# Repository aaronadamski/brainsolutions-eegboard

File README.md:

# brainsolutions-eegboard
EEG Prototype Board for UCI Senior Design

For use in KiCAD EDA Suite.

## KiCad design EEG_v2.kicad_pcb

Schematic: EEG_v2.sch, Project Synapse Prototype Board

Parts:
JP1: JUMPER; 2x1 0.1\"
P1, P6: CONN_2; 2x1 0.1\"
P2, P4: CONN_8; 8x1 0.1\"
P3: USB_A
P5: CONN_5X2; 5x2 0.1\"
P7: CONN_1
R1: 10K; 0603
SW1: SWITCH_INV; SSSS810701
SW2: RESET

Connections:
+3.3V: R1.1; also elsewhere on the board
/Analog Frontend/AIN1N: P2.2; also elsewhere on the board
/Analog Frontend/AIN1P: P2.1; also elsewhere on the board
/Analog Frontend/AIN2N: P2.4; also elsewhere on the board
/Analog Frontend/AIN2P: P2.3; also elsewhere on the board
/Analog Frontend/AIN3N: P2.6; also elsewhere on the board
/Analog Frontend/AIN3P: P2.5; also elsewhere on the board
/Analog Frontend/AIN4N: P2.8; also elsewhere on the board
/Analog Frontend/AIN4P: P2.7; also elsewhere on the board
/Analog Frontend/AIN5N: P4.2; also elsewhere on the board
/Analog Frontend/AIN5P: P4.1; also elsewhere on the board
/Analog Frontend/AIN6N: P4.4; also elsewhere on the board
/Analog Frontend/AIN6P: P4.3; also elsewhere on the board
/Analog Frontend/AIN7N: P4.6; also elsewhere on the board
/Analog Frontend/AIN7P: P4.5; also elsewhere on the board
/Analog Frontend/AIN8N: P4.8; also elsewhere on the board
/Analog Frontend/AIN8P: P4.7; also elsewhere on the board
/Analog Frontend/BIAS: P7.1; also elsewhere on the board
/Analog Frontend/SRB1: P6.1; also elsewhere on the board
/Analog Frontend/SRB2: P6.2 (PM); also elsewhere on the board
/BATT_+: P1.2 (PM), SW1.3
/Microcontroller/DC: P5.3; also elsewhere on the board
/Microcontroller/DD: P5.4; also elsewhere on the board
/Microcontroller/RESET_N: JP1.2, P5.7, SW2.3; also elsewhere on the board
/Microcontroller/USB_N: P3.2 (D-); also elsewhere on the board
/Microcontroller/USB_P: P3.3 (D+); also elsewhere on the board
/VBUS: P3.1 (VBUS), SW1.1
AGND: P1.1, P3.4 (GND), P3.5 (Shield), P3.6 (Shield), P5.1, SW2.1, SW2.2; also elsewhere on the board
unnamed: JP1.1, R1.2
VIN_RAW: P5.2, P5.9, SW1.2; also elsewhere on the board

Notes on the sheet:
BATT_-

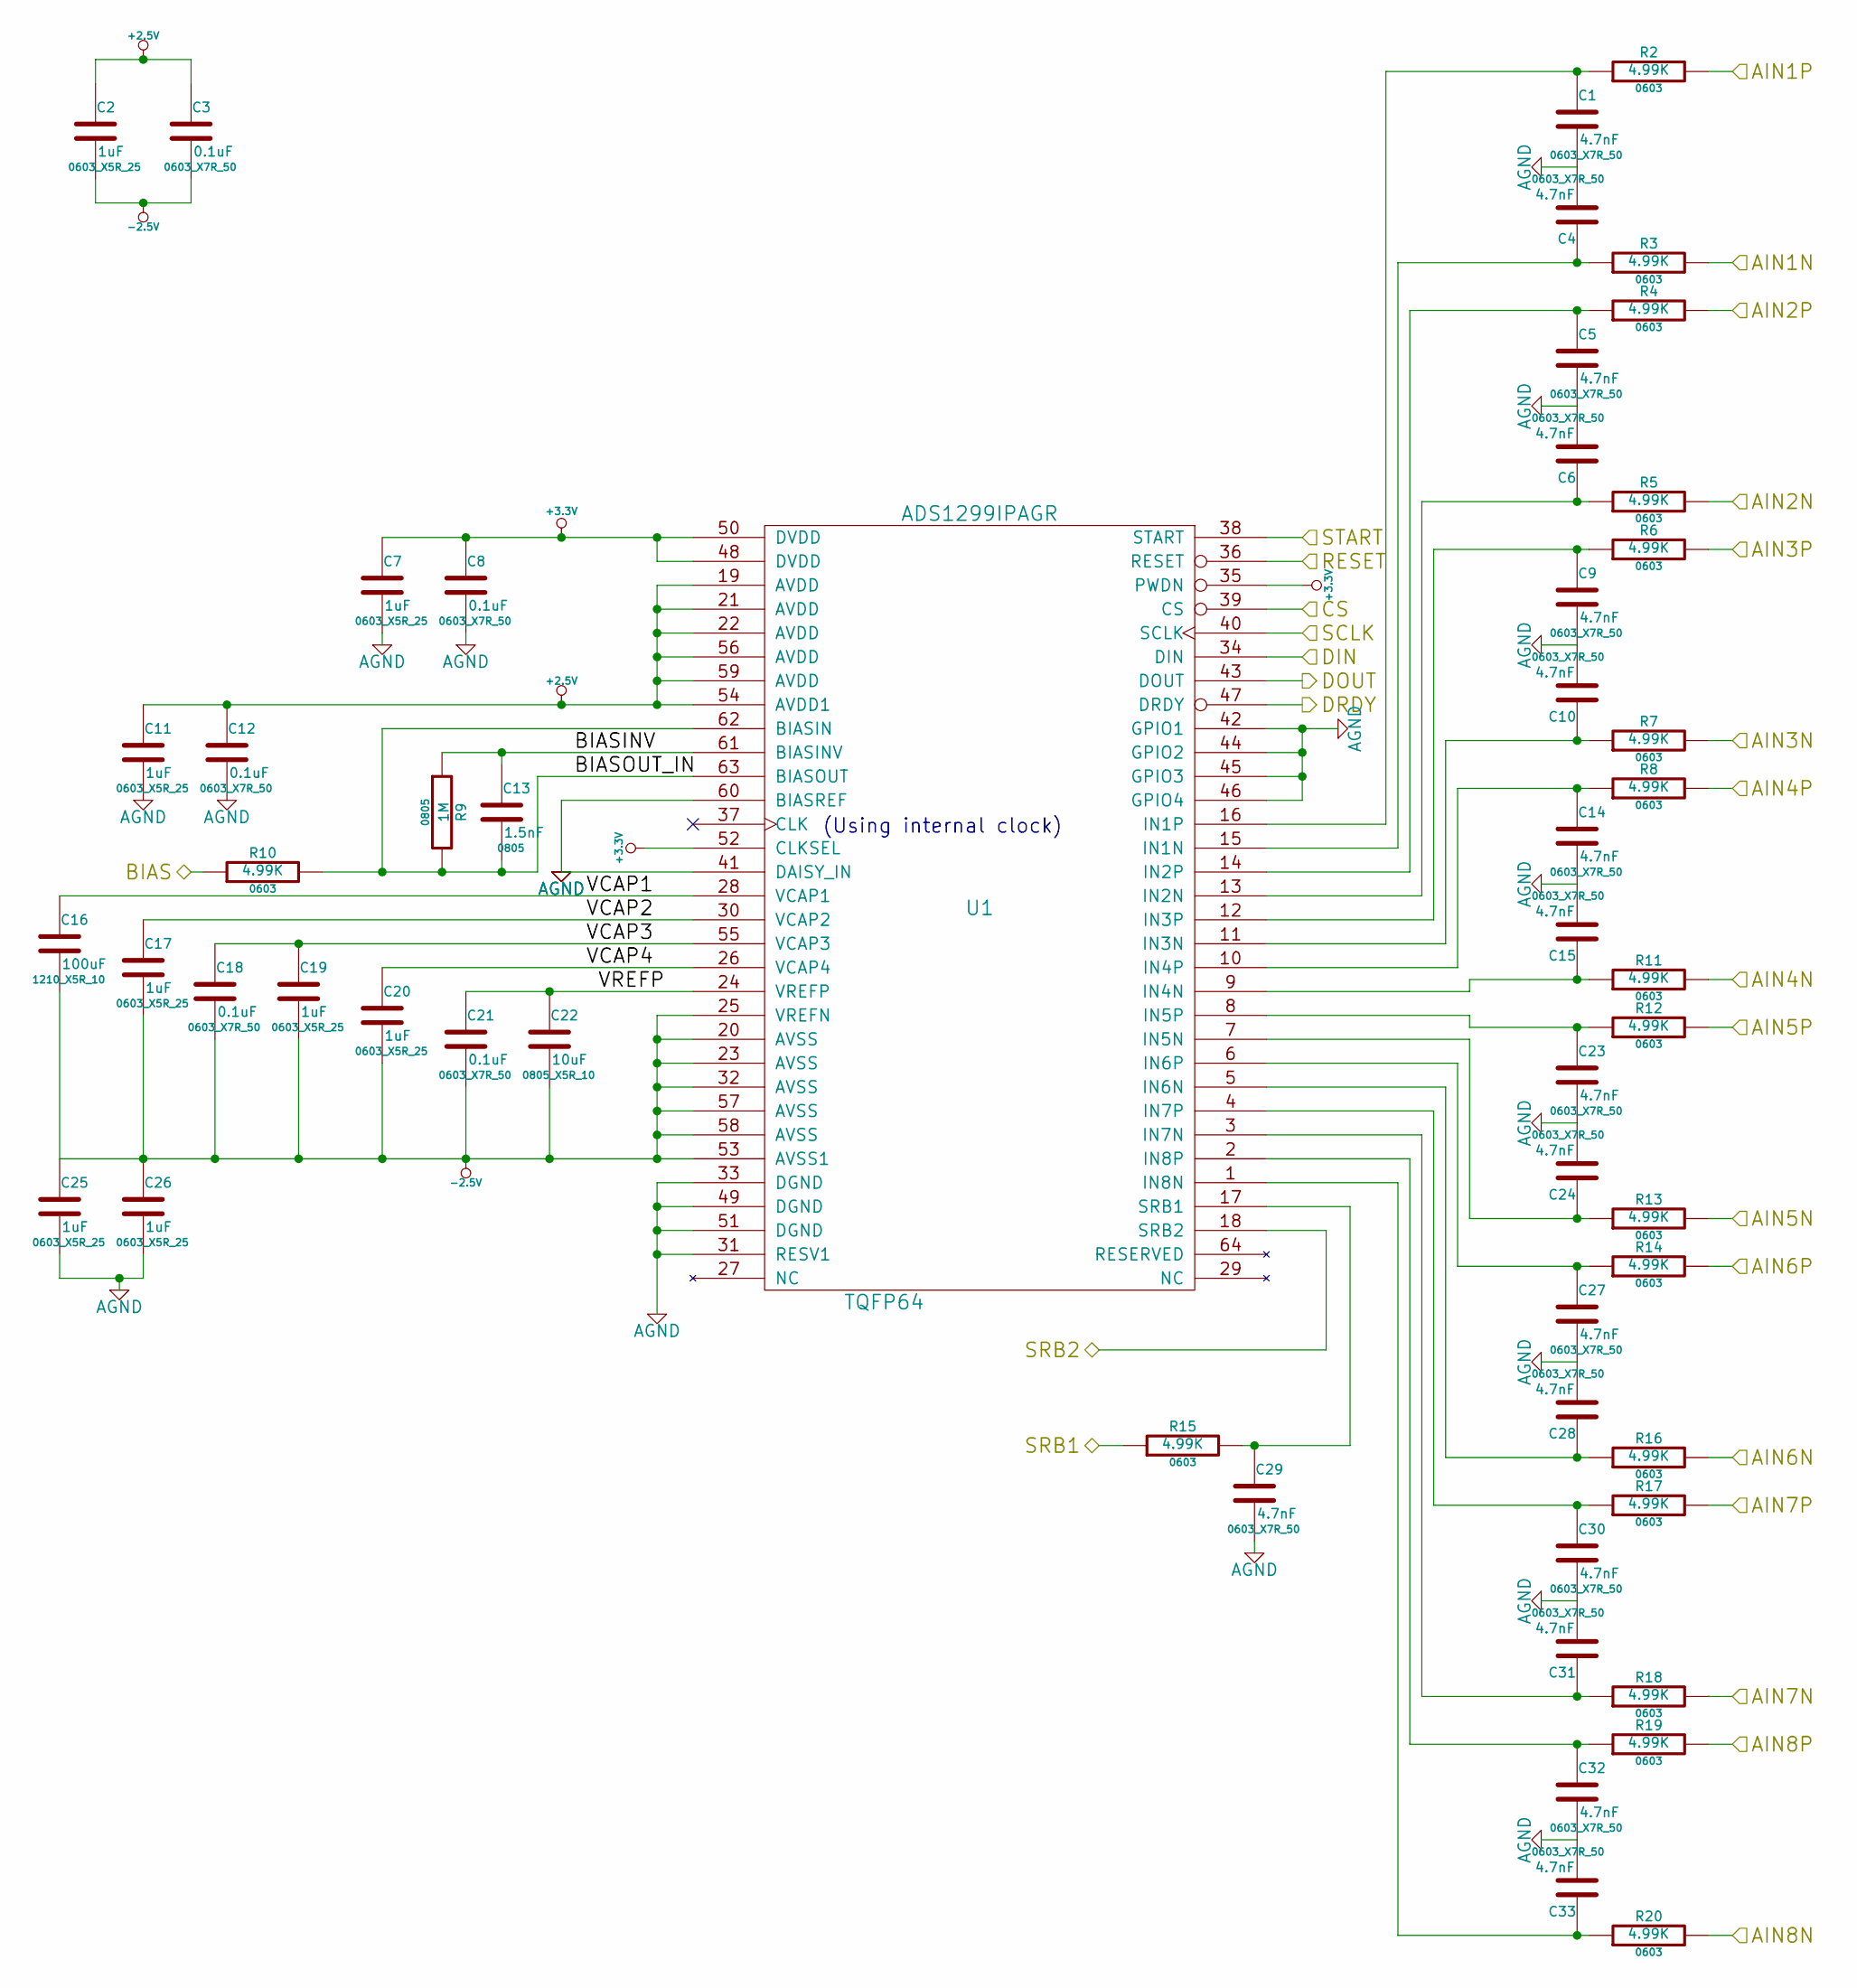
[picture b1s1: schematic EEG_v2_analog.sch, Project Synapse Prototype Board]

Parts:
C1, C4, C5, C6, C9, C10, C14, C15, C23, C24, C27, C28, C29, C30, C31, C32, C33: 4.7nF; 0603_X7R_50
C2, C7, C11, C17, C19, C20, C25, C26: 1uF; 0603_X5R_25
C3, C8, C12, C18, C21: 0.1uF; 0603_X7R_50
C13: 1.5nF; 0805
C16: 100uF; 1210_X5R_10
C22: 10uF; 0805_X5R_10
R2, R3, R4, R5, R6, R7, R8, R10, R11, R12, R13, R14, R15, R16, R17, R18, R19, R20: 4.99K; 0603
R9: 1M; 0805
U1: ADS1299IPAGR; TQFP64

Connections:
+2.5V: C2.1, C3.1, C11.1, C12.1, U1.19 (AVDD), U1.21 (AVDD), U1.22 (AVDD), U1.54 (AVDD1), U1.56 (AVDD), U1.59 (AVDD); also elsewhere on the board
+3.3V: C7.1, C8.1, U1.35 (PWDN), U1.48 (DVDD), U1.50 (DVDD), U1.52 (CLKSEL); also elsewhere on the board
-2.5V: C2.2, C3.2, C16.2, C17.2, C18.2, C19.2, C20.2, C21.2, C22.2, C25.1, C26.1, U1.20 (AVSS), U1.23 (AVSS), U1.25 (VREFN), U1.32 (AVSS), U1.53 (AVSS1), U1.57 (AVSS), U1.58 (AVSS); also elsewhere on the board
/Analog Frontend/AIN1N: R3.2; also elsewhere on the board
/Analog Frontend/AIN1P: R2.2; also elsewhere on the board
/Analog Frontend/AIN2N: R5.2; also elsewhere on the board
/Analog Frontend/AIN2P: R4.2; also elsewhere on the board
/Analog Frontend/AIN3N: R7.2; also elsewhere on the board
/Analog Frontend/AIN3P: R6.2; also elsewhere on the board
/Analog Frontend/AIN4N: R11.2; also elsewhere on the board
/Analog Frontend/AIN4P: R8.2; also elsewhere on the board
/Analog Frontend/AIN5N: R13.2; also elsewhere on the board
/Analog Frontend/AIN5P: R12.2; also elsewhere on the board
/Analog Frontend/AIN6N: R16.2; also elsewhere on the board
/Analog Frontend/AIN6P: R14.2; also elsewhere on the board
/Analog Frontend/AIN7N: R18.2; also elsewhere on the board
/Analog Frontend/AIN7P: R17.2; also elsewhere on the board
/Analog Frontend/AIN8N: R20.2; also elsewhere on the board
/Analog Frontend/AIN8P: R19.2; also elsewhere on the board
/Analog Frontend/BIAS: R10.1; also elsewhere on the board
/Analog Frontend/BIASINV: C13.1, R9.1, U1.61 (BIASINV)
/Analog Frontend/BIASOUT_IN: C13.2, R9.2, R10.2, U1.62 (BIASIN), U1.63 (BIASOUT)
/Analog Frontend/CS: U1.39 (CS); also elsewhere on the board
/Analog Frontend/DIN: U1.34 (DIN); also elsewhere on the board
/Analog Frontend/DOUT: U1.43 (DOUT); also elsewhere on the board
/Analog Frontend/DRDY: U1.47 (DRDY); also elsewhere on the board
/Analog Frontend/RESET: U1.36 (RESET); also elsewhere on the board
/Analog Frontend/SRB1: R15.1; also elsewhere on the board
/Analog Frontend/SRB2: U1.18 (SRB2); also elsewhere on the board
/Analog Frontend/START: U1.38 (START); also elsewhere on the board
/Analog Frontend/VCAP1: C16.1, U1.28 (VCAP1)
/Analog Frontend/VCAP2: C17.1, U1.30 (VCAP2)
/Analog Frontend/VCAP3: C18.1, C19.1, U1.55 (VCAP3)
/Analog Frontend/VCAP4: C20.1, U1.26 (VCAP4)
/Analog Frontend/VREFP: C21.1, C22.1, U1.24 (VREFP)
/Microcontroller/SCK: U1.40 (SCLK); also elsewhere on the board
AGND: C1.2, C4.2, C5.2, C6.2, C7.2, C8.2, C9.2, C10.2, C11.2, C12.2, C14.2, C15.2, C23.2, C24.2, C25.2, C26.2, C27.2, C28.2, C29.2, C30.2, C31.2, C32.2, C33.2, U1.31 (RESV1), U1.33 (DGND), U1.41 (DAISY_IN), U1.42 (GPIO1), U1.44 (GPIO2), U1.45 (GPIO3), U1.46 (GPIO4), U1.49 (DGND), U1.51 (DGND), U1.60 (BIASREF); also elsewhere on the board
unnamed: C9.1, R6.1, U1.12 (IN3P)
unnamed: C1.1, R2.1, U1.16 (IN1P)
unnamed: C4.1, R3.1, U1.15 (IN1N)
unnamed: C10.1, R7.1, U1.11 (IN3N)
unnamed: C5.1, R4.1, U1.14 (IN2P)
unnamed: C6.1, R5.1, U1.13 (IN2N)
unnamed: C29.1, R15.2, U1.17 (SRB1)
unnamed: C32.1, R19.1, U1.2 (IN8P)
unnamed: C33.1, R20.1, U1.1 (IN8N)
unnamed: C27.1, R14.1, U1.6 (IN6P)
unnamed: C28.1, R16.1, U1.5 (IN6N)
unnamed: C30.1, R17.1, U1.4 (IN7P)
unnamed: C31.1, R18.1, U1.3 (IN7N)
unnamed: C15.1, R11.1, U1.9 (IN4N)
unnamed: C14.1, R8.1, U1.10 (IN4P)
unnamed: C23.1, R12.1, U1.8 (IN5P)
unnamed: C24.1, R13.1, U1.7 (IN5N)

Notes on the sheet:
(Using internal clock)

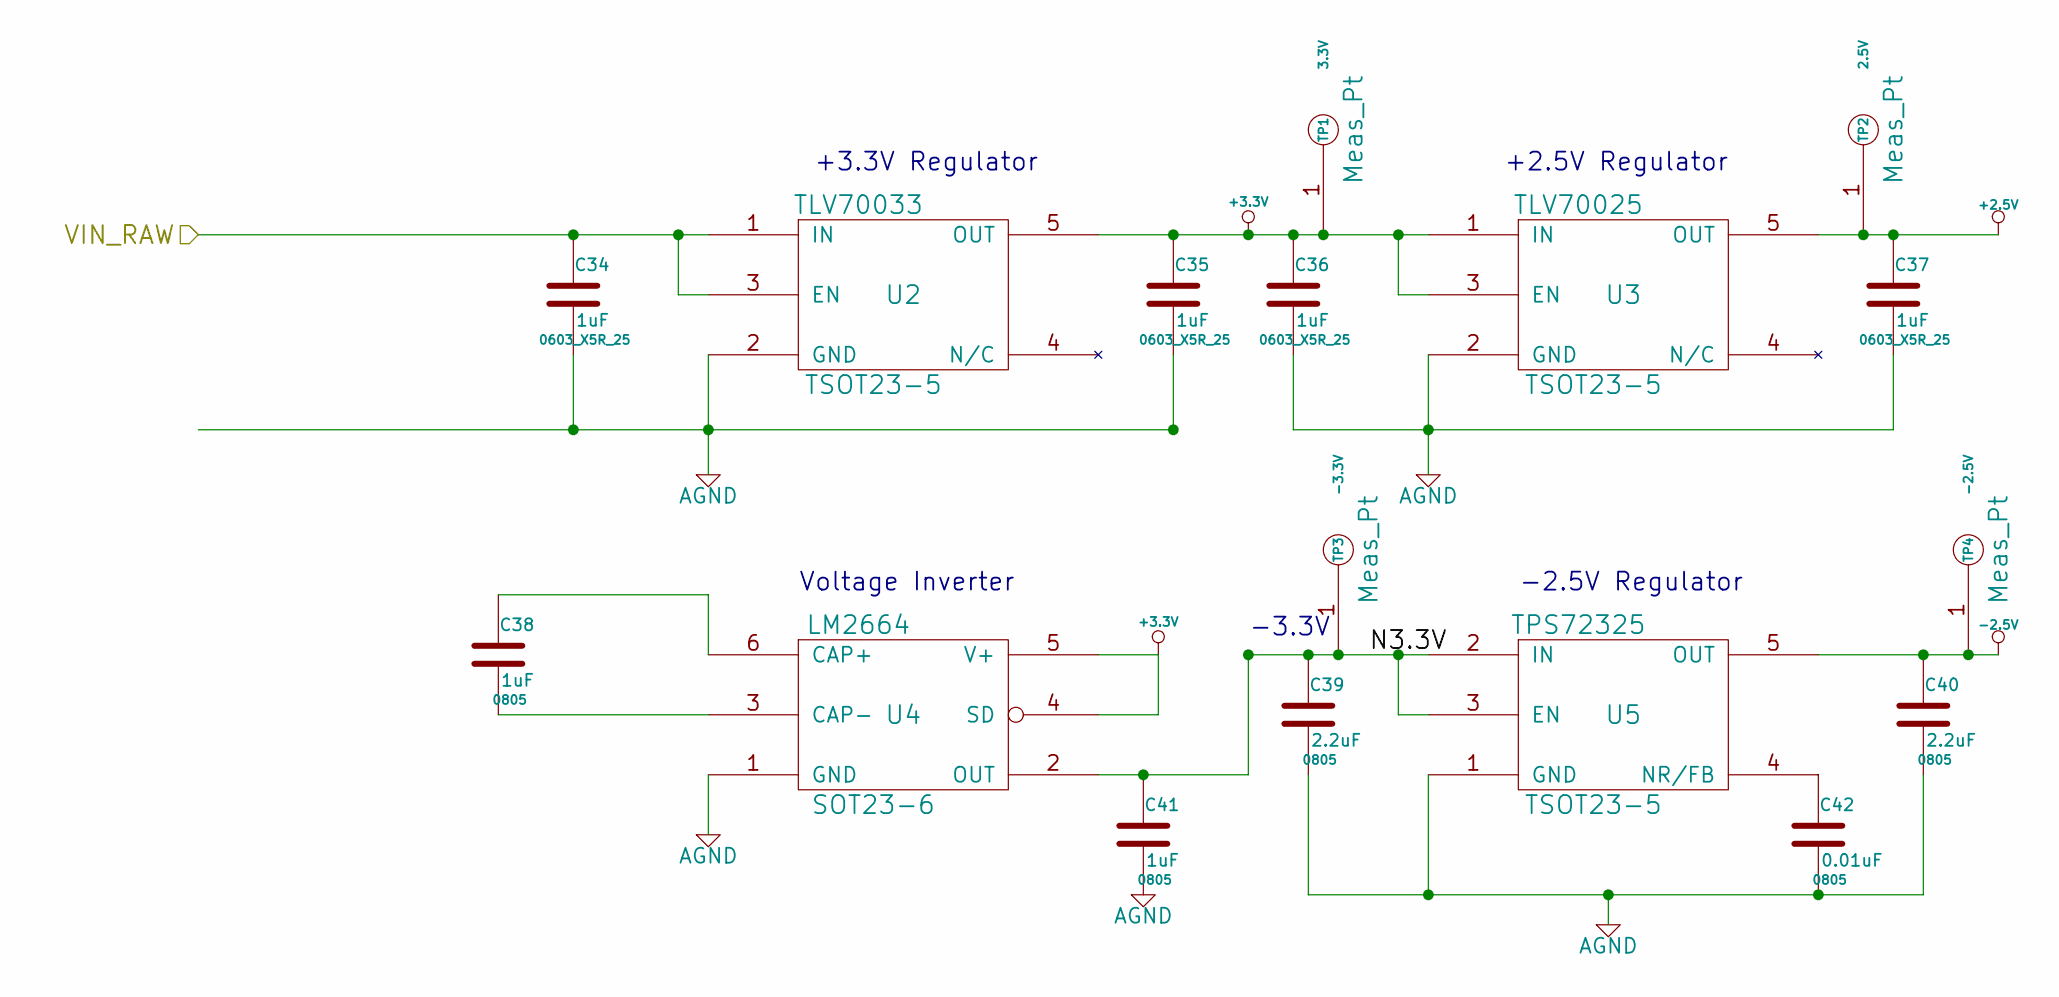
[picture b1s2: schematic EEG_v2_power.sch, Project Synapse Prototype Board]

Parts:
C34, C35, C36, C37: 1uF; 0603_X5R_25
C38, C41: 1uF; 0805
C39, C40: 2.2uF; 0805
C42: 0.01uF; 0805
TP1: 3.3V; Meas_Pt
TP2: 2.5V; Meas_Pt
TP3: -3.3V; Meas_Pt
TP4: -2.5V; Meas_Pt
U2: TLV70033; TSOT23-5
U3: TLV70025; TSOT23-5
U4: LM2664; SOT23-6
U5: TPS72325; TSOT23-5

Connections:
+2.5V: C37.1, TP2.1, U3.5 (OUT); also elsewhere on the board
+3.3V: C35.1, C36.1, TP1.1, U2.5 (OUT), U3.1 (IN), U3.3 (EN), U4.4 (SD), U4.5 (V+); also elsewhere on the board
-2.5V: C40.1, TP4.1, U5.5 (OUT); also elsewhere on the board
/Power/N3.3V: C39.1, C41.1, TP3.1, U4.2 (OUT), U5.2 (IN), U5.3 (EN)
AGND: C34.2, C35.2, C36.2, C37.2, C39.2, C40.2, C41.2, C42.2, U2.2 (GND), U3.2 (GND), U4.1 (GND), U5.1 (GND); also elsewhere on the board
unnamed: C42.1, U5.4 (NR/FB)
unnamed: C38.1, U4.6 (CAP+)
unnamed: C38.2, U4.3 (CAP-)
VIN_RAW: C34.1, U2.1 (IN), U2.3 (EN); also elsewhere on the board

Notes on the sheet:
+3.3V Regulator
+2.5V Regulator
Voltage Inverter
-3.3V
-2.5V Regulator

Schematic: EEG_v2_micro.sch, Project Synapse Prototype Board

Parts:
A1: AN043
C43, C44, C45, C46, C47, C48, C49, C50, C53: 1u; 0402_X5R_K_6P3
C51, C52: 15p; 0402_NP0_J_50
C54, C55: 47p; 0402_NP0_J_50
C56: 0.5p; 0402_NP0_B_50
C57, C58: 12p; 0402_NP0_J_50
C59: 1n; 0402_NP0_J_50
D1: LED_EL19-21SURC; 0603
D2: LED_EL19-21SYGC; 0603
L1: EMI; 0402
R21: 0; 0402
R22: 56k; 0402_F
R23, R24: 33; 0402_G
R25, R26: 270; 0402_F
R27: 2.2k; 0402_G
SW3, SW4: SW_PUSH_4PIN
U6: CC2540; VQFN40
U7: 2450BM15A0002E
X1: QUARTZCMS4_32K
X2: QUARTZCMS4_MOD

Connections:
+3.3V: L1.2; also elsewhere on the board
/Analog Frontend/CS: U6.18 (P0_1); also elsewhere on the board
/Analog Frontend/DIN: U6.15 (P0_4); also elsewhere on the board
/Analog Frontend/DOUT: U6.14 (P0_5); also elsewhere on the board
/Analog Frontend/DRDY: U6.13 (P0_6); also elsewhere on the board
/Analog Frontend/RESET: U6.12 (P0_7); also elsewhere on the board
/Analog Frontend/START: U6.19 (P0_0); also elsewhere on the board
/Microcontroller/ANTENNA: A1.1 (FEED), R21.2
/Microcontroller/DC: U6.34 (P2_2); also elsewhere on the board
/Microcontroller/DD: U6.35 (P2_1); also elsewhere on the board
/Microcontroller/LED1: R25.2, U6.9 (P1_1)
/Microcontroller/LED2: R26.2, U6.11 (P1_0)
/Microcontroller/RESET_INTR: C59.1, R27.1, U6.20 (RESET_N)
/Microcontroller/RESET_N: R27.2; also elsewhere on the board
/Microcontroller/RF_N: U6.26 (RF_N), U7.3 (Balanced)
/Microcontroller/RF_P: U6.25 (RF_P), U7.4 (Balanced)
/Microcontroller/SCK: U6.16 (P0_3); also elsewhere on the board
/Microcontroller/SW3: SW3.4, U6.7 (P1_3)
/Microcontroller/SW4: SW4.3, U6.8 (P1_2)
/Microcontroller/TX_LINE: C56.1, R21.1, U7.1 (Unbalanced)
/Microcontroller/USB_N: R24.1; also elsewhere on the board
/Microcontroller/USB_N_Intr: C55.1, R24.2, U6.3 (USB_N)
/Microcontroller/USB_P: R23.1; also elsewhere on the board
/Microcontroller/USB_P_Intr: C54.2, R23.2, U6.2 (USB_P)
/Microcontroller/VDD_FILT: C43.1, C44.1, C45.1, C46.1, C47.1, C48.1, C49.1, C50.1, L1.1, U6.4 (DVDD_USB), U6.10 (DVDD2), U6.21 (AVDD5), U6.24 (AVDD3), U6.27 (AVDD2), U6.28 (AVDD1), U6.29 (AVDD4), U6.31 (AVDD6), U6.39 (DVDD1)
/Microcontroller/X1_1: C51.1, U6.33 (P2_3/XOSC32K_Q1), X1.1
/Microcontroller/X1_2: C52.1, U6.32 (P2_4/XOSC32K_Q1), X1.2
/Microcontroller/X2_1: C57.1, U6.22 (XOSC_Q1), X2.1
/Microcontroller/X2_3: C58.1, U6.23 (XOSC_Q2), X2.3
AGND: A1.2 (GND), C43.2, C44.2, C45.2, C46.2, C47.2, C48.2, C49.2, C50.2, C51.2, C52.2, C53.2, C54.1, C55.2, C56.2, C57.2, C58.2, C59.2, D1.2 (K), D2.2 (K), R22.2, SW3.1, SW3.2, SW4.1, SW4.2, U6.1 (DGND_USB), U6.41 (PAD), U7.2 (GND), U7.5 (GND), U7.6 (GND), X2.2, X2.4; also elsewhere on the board
unnamed: R22.1, U6.30 (R_BIAS)
unnamed: C53.1, U6.40 (DCOUPL)
unnamed: D1.1 (A), R25.1
unnamed: D2.1 (A), R26.1

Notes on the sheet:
LED RED
LED GREEN

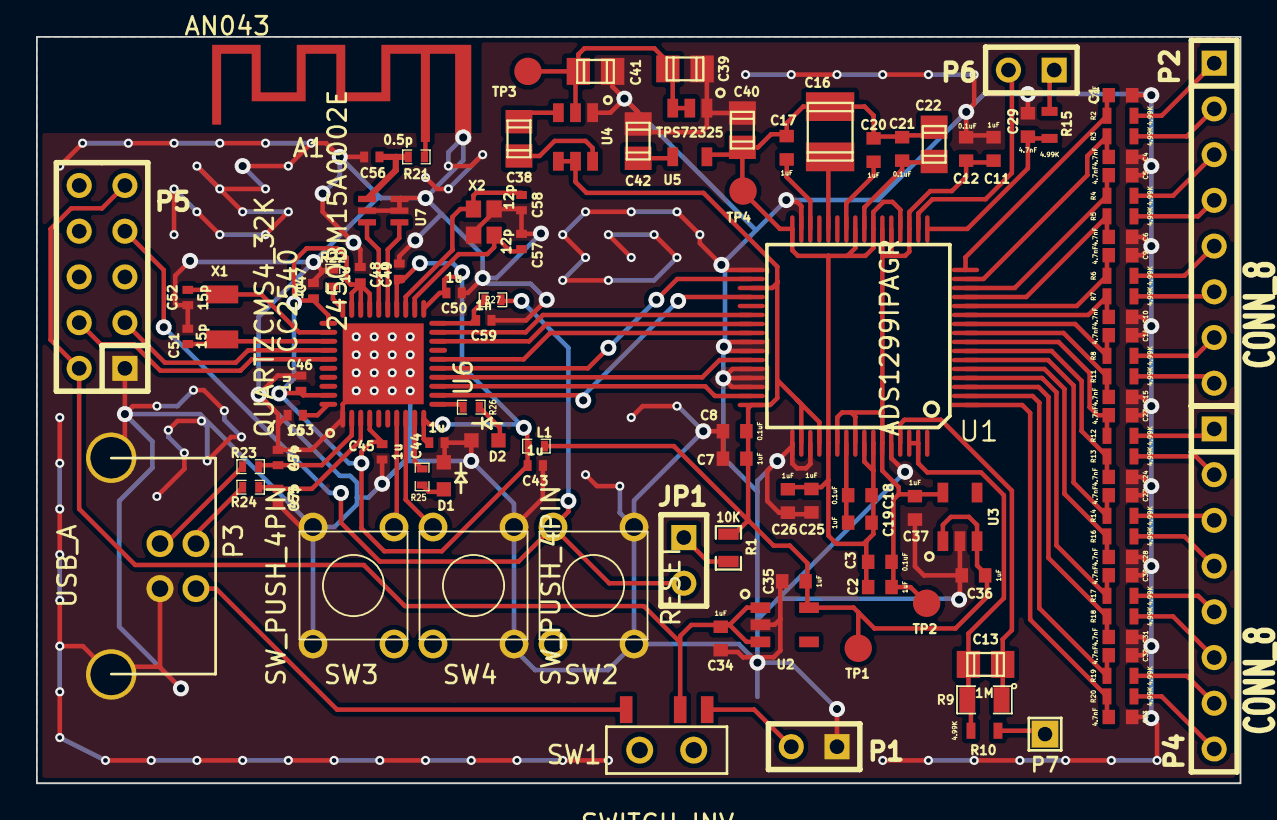
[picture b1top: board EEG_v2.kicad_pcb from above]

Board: 2 copper layers, 66.9 x 41.5 mm, 115 parts (0 on the bottom side), 87 nets.

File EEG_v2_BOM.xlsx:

PrePurch? | ref | Quantity | value | Manufacturer | Part Number | footprint
N | C56 | 1 | 0.5p | Murata | GRM1555C1HR50BZ01D | 0402_NP0_B_50
N | C57 C58 | 2 | 12p | Murata | GRM1555C1H120JA01D | 0402_NP0_J_50
N | C51 C52 | 2 | 15p | Murata | GRM1555C1H150JA01D | 0402_NP0_J_50
N | C54 C55 | 2 | 47p | Murata | GRM1555C1H470JA01D | 0402_NP0_J_50
N | C59 | 1 | 1n | Murata | GRM1555C1H102JA01D | 0402_NP0_J_50
Y | C13 | 1 | 1.5nF | AVX | 08055C152KAT2A | 0805
N | C1 C4 C5 C6 C9 C10 C14 C15 C23 C24 C27 C28 C29 C30 C31 C32 C33 | 17 | 4.7nF | Murata | GRM188R71H472KA01D | 0603_X7R_50
Y | C42 | 1 | 0.01uF | AVX | 08055C103KAT2A | 0805
N | C3 C8 C12 C18 C21 | 5 | 0.1uF | Murata | GRM188R71H104KA93D | 0603_X7R_50
N | C43 C44 C45 C46 C47 C48 C49 C50 C53 | 9 | 1u | Murata | GRM155R60J105KE19D | 0402_X5R_K_6P3
N | C2 C7 C11 C17 C19 C20 C25 C26 C34 C35 C36 C37 | 12 | 1uF | Murata | GRM188R61E105KA12D | 0603_X5R_25
Y | C38 C41 | 2 | 1uF | AVX | 08055YC105KAT2A | 0805
Y | C39 C40 | 2 | 2.2uF | AVX | 0805ZD225MAT2A | 0805
Y | C22 | 1 | 10uF | AVX | 08056D106MAT2A | 0805_X5R_10
Y | C16 | 1 | 100uF | AVX | F930J107MBA | 1210_X5R_10
N | D1 | 1 | LED_EL19-21SURC | Everlight | EL-19-21SURC/S530-A2/TR8 | 0603
N | D2 | 1 | LED_EL19-21SYGC | Everlight | 19-21SYGC/S530-E1/TR8 | 0603
 | JP1 | 1 | JUMPER |  |  | 2x1 0.1"
N | L1 | 1 | EMI | Murata | BLM15HG102SN1D | 0402
 | P1 | 1 | CONN_2 |  |  | 2x1 0.1"
 | P6 | 1 | CONN_3 |  |  | 3x1 0.1"
N | P3 | 1 | USB-MINI-B | Molex | 47346-0001 | 47346-0001
 | P5 | 1 | CONN_5X2 |  |  | 5x2 0.1"
 | P2 P4 | 2 | CONN_8 |  |  | 8x1 0.1" |  |  |  | Footprints to do
N | R21 | 1 | 0 | KOA | RK73Z1ETTP | 402 |  |  | x | 2x1 0.1"
N | R23 R24 | 2 | 33 | KOA | RK73H1ETTP33R0F | 0402_G |  |  | x | 8x1 0.1"
N | R25 R26 | 2 | 270 | KOA | RK73H1ETTP2700F | 0402_F |  |  | x | 3x1 0.1"
N | R27 | 1 | 2.2k | KOA | RK73H1ETTP2201F | 0402_G |  |  | x | 5x2 0.1"
N | R2 R3 R4 R5 R6 R7 R8 R10 R11 R12 R13 R14 R15 R16 R17 R18 R19 R20 | 18 | 4.99K | Vishay | CRCW06034K99FKEA | 0603 |  |  | x | 47346-0001
N | R1 | 1 | 10K | Vishay | CRCW060310K0FKEA | 0603 |  |  | x | thru 1825910
N | R22 | 1 | 56k | KOA | RK73H1ETTP5602F | 0402_F |  |  | x | VQFN40
Y | R9 | 1 | 1M | Vishay | CRCW08051M00FKEA | 0805 |  |  |  | 2450bm15a0002e
N | SW1 | 1 | SWITCH_INV | ALPS | SSSS810701 | SSSS810701 |  |  | x | crystal1
 | SW2 | 1 | RESET | TE Connectivity | 2-1825910-7 | Thru 1825910 |  |  | x | crystal2
N | SW3 SW4 | 2 | SW_PUSH | TE Connectivity | 2-1825910-7 | Thru 1825910 |  |  | x | ssss810701
 | TP2 | 1 | 2.5V |  | N/A | Meas_Pt
 | TP1 | 1 | 3.3V |  | N/A | Meas_Pt
 | TP3 | 1 | -3.3V |  | N/A | Meas_Pt
 | TP4 | 1 | -2.5V |  | N/A | Meas_Pt
N | U7 | 1 | 2450BM15A0002E | Johanson | 2450BM15A0002E | 2450BM15A0002E
Y | U4 | 1 | LM2664 | TI | LM2664M6X/NOPB | SOT23-6
Y | U1 | 1 | ADS1299IPAGR | TI | ADS1299IPAGR | TQFP64
Y | U2 | 1 | TLV70033 | TI | TLV70033DDCR | TSOT23-5
Y | U3 | 1 | TLV70025 | TI | TLV70025DDCR | TSOT23-5
Y | U5 | 1 | TPS72325 | TI | TPS72325DBVR | TSOT23-5
Y | U6 | 1 | CC2540 | TI | CC2540F256RHAR | VQFN40
N | X2 | 1 | 32-MHz | Epson | FA-128 32.0000MF20X-K3 | 10/20/60/10
N | X1 | 1 | 32.768-KHz | Epson | FC-135 32.7680KA-A3 | ~

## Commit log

2015-01-12 :circus_tent: Added .gitattributes & .gitignore files
2015-01-12 First Commit
    Copied from v1 prototype
2015-01-12 Created Hierarchy of Sheets
    Divided by power, analog, and microcontroller
2015-01-12 Added Datasheets and Application Note for Antenna
    swra117d - antenna design reference
2015-01-13 Added CC2540 Bluetooth chip to library
    Also added CC2540 to sch
2015-01-13 Finished CC2540 Symbol, Added example application schematic
2015-01-13 Pin connect, add note on Balun and antenna
2015-01-14 Testing commit from laptop.
2015-01-14 Following TI Reference design CC2540EM. Added component footprints on micro sheet.
2015-01-15 Finished copy of reference design. Still need to figure out what to do with USB pins. Added Johanson balun.
2015-01-15 Added USB connection.
2015-01-15 Add reference designs.
2015-01-15 Added capacitors for USB.
2015-01-23 Microcontroller Sheet Work
    Add antenna components and label. Add debug flash hier pins. Add RC
    filter for RESET_N pin. Add heir labels for USB.
2015-01-23 Main sheet cleanup
    Add pins for raw vin and GND for power switching between USB and
    battery.
2015-01-23 Add USB Connector
    Added desc of USB A connector
2015-01-24 Add battery connectors and switch
2015-01-24 Added debug / programming connector
2015-01-24 Add note to debug connector for possible change.
2015-01-24 Changed color of labels to be visible against bg.
2015-01-24 Created netlist file to test footprint associations.
2015-01-24 Add symbol and footprints for SMD test points.
    Add test points to power supplies.
2015-01-24 Added footprints to ADS caps, shorted unused GPIO to gnd
2015-01-24 Add decoupling caps btwn AVDD and AVSS
2015-01-24 Clean ERC errors.
2015-01-27 Added patient protection resistors and filter caps to input electroes
2015-01-27 Added pins for bias and SRB1/2
2015-01-27 Add RC to SRB1
2015-01-27 Imported sheet pins to main sheet
2015-01-27 Add pin headers for electrodes and debug signals.
2015-01-27 Correct pin headers
2015-01-28 Modify libraries to be correct. Add pushbuttons and LEDs. Change switch to toggle.
2015-01-28 Fix ERC. Generate netlist.
2015-01-29 Added footprint designators for voltage regulators.
2015-01-29 add eval ref design for cc2540.
2015-01-29 Add reset button / jumper
2015-01-29 Unnecessary save
2015-01-29 Add footprints
2015-01-29 Added footprints to connectors. Changed usb A to usb micro B
2015-01-29 Modified Vbus on usb conn to be power out. Replaced batt connections with 0.1" headers
2015-01-29 Add footprints for tactile switches
2015-01-29 Add datasheet for power switch, footprints for test points
2015-01-29 Add balun datasheet
2015-01-29 Correct 32k crystal
2015-01-30 Associate footprints to pcbnew
2015-01-30 Made some footprints
2015-01-30 Create CC2540 footprint and edit pad name
2015-01-30 Association of footprints. Add footprints, one left. Add datasheets. Update BOM
2015-01-31 Begin layout. Finish footprints and association.
2015-02-01 Continued layout work.
2015-02-01 Change USB connector. Continue layout.
2015-02-01 Change layout.
2015-02-01 Continue layout on ADS side, power supplies complete.
2015-02-01 Name nets for convenience on CC2540.
2015-02-02 Continue layout.
2015-02-02 Continue layout for CC2540
    Change swiches to one pin operating to clear under space. Edit USB conn
    to show back size.
2015-02-03 Continue layout, compress chips together.
2015-02-03 Continue layout and add antenna
2015-02-03 Continue layout. Add fill zones.
2015-02-03 Add autoroute version
2015-02-03 add auto verison
2015-02-03 Tested autorouter. ehhhh.
2015-02-04 Continue layout, test antenna workings
2015-02-04 Continue layout experiment with add antenna
2015-02-04 Nearly finished layout
2015-02-04 Final layout submitted.
